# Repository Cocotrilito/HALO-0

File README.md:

# HALO-0
HALO-0 is a custom development board built around the RP2040 System-on-Chip (SoC).this features a quad memory flash a crystal oscillator, a voltage regulator and a USB C. adding to the repos thematic the HALO-0 has a quote of doubting the impossible and a masterpiece, NAPOLEON TO THE MUNA!

## The reason behind this project
This project started as a following up to the guide provided by *https://github.com/KaiPereira* the teacher or the one for making this project possible, basically my goal was to learn the fundamentals of schematic and routing, and learn everything about how an actual pcb works, cause I've already made two, but really basic ones.. so with this project I was able to open more my eyes, and learn a bit more about everything (USB, MEMORY FLASH, CRYSTAL OSCILATORS, VOLTAGE REGULATORS, CAPACITORS, RESISTANCES, ETC). BUT I did not ended there so I added my OWN style of art, based on my personal preferences (napoleon). and I also added a quote that helped me be disciplined with HackClub Stasis!. its an easter egg hahaha.

## Schematic Overview

this is the schematic 

-

## PCB - DIFERENT VERSIONS

## RENDER!!

## BOM

| Name | Purpose | Qty | Cost (USD) | Distributor
|-----:|----------|----------|-------|-------|
| RP2040 (U1) | Brain of the PCB | 1 | $4.89 | JLCPCB / LCSC |
| W25Q16JVUXIQ | Memory for the PCB | 1 | $5.07 | JLCPCB / LCSC |
| TYPE-C-31-M-12 | USB C Energy & Data | 1 | $0.91 | JLCPCB / LCSC |
| KT-0603R (D1) | LED RED (Cohete Art) | 1 | $0.03 | JLCPCB / LCSC |
|RC0603JR-071KL (R8) | 1k LED resistor | 1 | $0.03 | JLCPCB / LCSC |
| MCP1700T-3302E/TT | Voltage regulator | 1 | $2.43 | JLCPCB / LCSC |
| X322512MSB4SI | Crystal 12Mhz | 1| $0.36 | JLCPCB / LCSC |
| TS-1088-AR02016 | SMD BUTTON | 2 | $0.27 | JLCPCB / LCSC |
| C13-14 10uF | Regulator capacitor | 2 | $0.01 | JLCPCB / LCSC |
| "C1, C10 1uF" | Energy input +1v1 | 2 | $0.01 | JLCPCB / LCSC |
| C2-C9 100nF | Decoupling caps | 8 | $0.01 | JLCPCB / LCSC |

## Final notes!
Thanks for reading! made possible with http://stasis.hackclub.com/
-/
## me
*By cocotrilo*
**made with luv (THIS ONE WAS WITH HATE) jk <3**

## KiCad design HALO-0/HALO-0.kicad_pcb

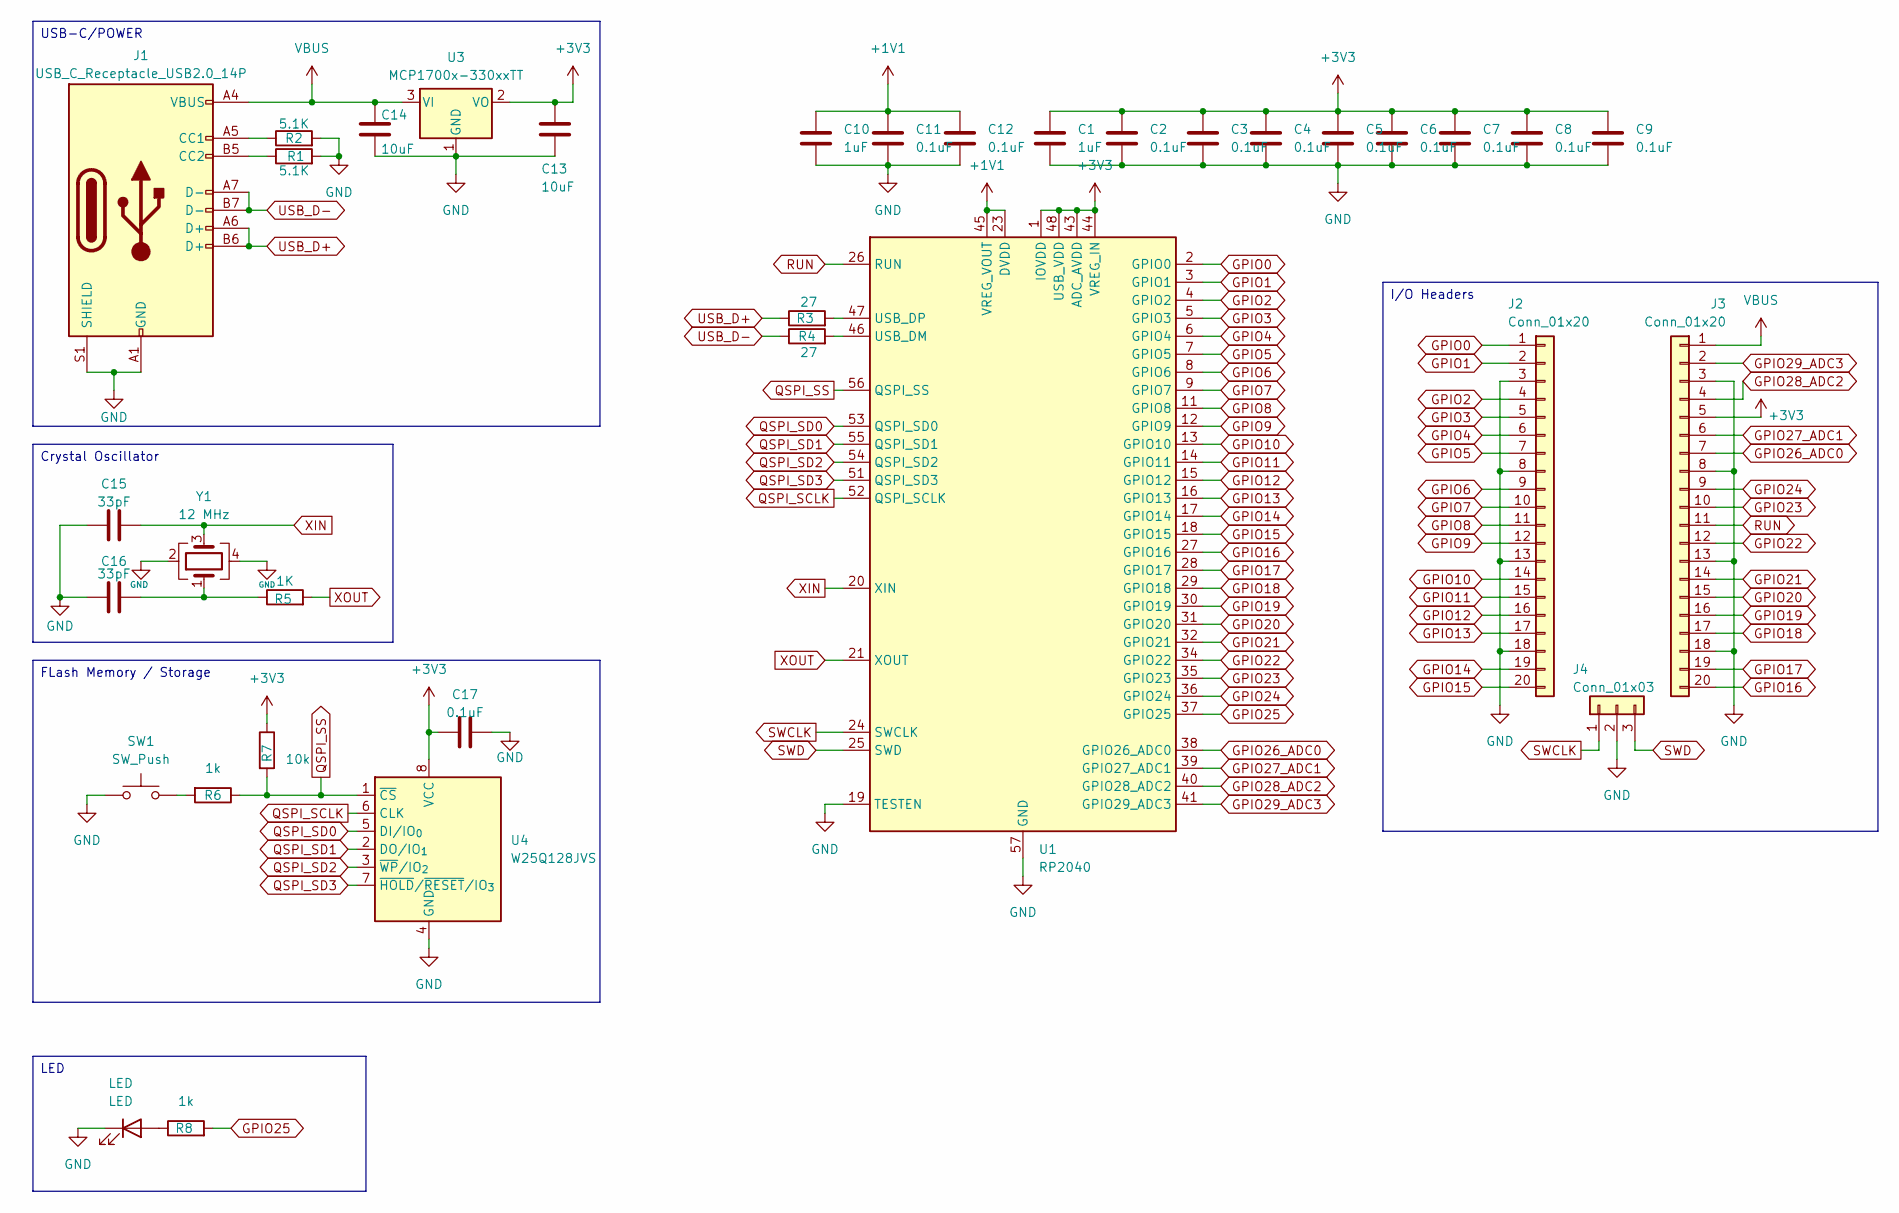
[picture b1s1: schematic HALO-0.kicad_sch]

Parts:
C1, C10: 1uF; C_0402_1005Metric
C2, C3, C4, C5, C6, C7, C8, C9, C11, C12, C17: 0.1uF; C_0402_1005Metric
C13, C14: 10uF; C_0603_1608Metric
C15, C16: 33pF; C_0402_1005Metric
J1: USB_C_Receptacle_USB2.0_14P; USB_C_Receptacle_HRO_TYPE-C-31-M-12
J2, J3: Conn_01x20; PinHeader_1x20_P2.54mm_Vertical
J4: Conn_01x03; PinHeader_1x03_P2.54mm_Vertical
LED: LED; LED_0603_1608Metric
R1, R2: 5.1K; R_0402_1005Metric
R3, R4: 27; R_0402_1005Metric
R5: 1K; R_0402_1005Metric
R6: 1k; R_0402_1005Metric
R7: 10k; R_0402_1005Metric
R8: 1k; R_0603_1608Metric
SW1: SW_Push; SW_Push_SPST_NO_Alps_SKRK
U1: RP2040; QFN-56-1EP_7x7mm_P0.4mm_EP3.2x3.2mm
U3: MCP1700x-330xxTT; SOT-23
U4: W25Q128JVS; Winbond_USON-8-1EP_3x2mm_P0.5mm_EP0.2x1.6mm
Y1: 12 MHz; Crystal_SMD_3225-4Pin_3.2x2.5mm

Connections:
+1V1: C10.1, C11.1, C12.1, U1.23 (DVDD), U1.45 (VREG_VOUT), U1.50 (DVDD)
+3V3: C1.1, C2.1, C3.1, C4.1, C5.1, C6.1, C7.1, C8.1, C9.1, C13.1, C17.1, J3.5, R7.1, U1.1 (IOVDD), U1.10 (IOVDD), U1.22 (IOVDD), U1.33 (IOVDD), U1.42 (IOVDD), U1.43 (ADC_AVDD), U1.44 (VREG_IN), U1.48 (USB_VDD), U1.49 (IOVDD), U3.2 (VO), U4.8 (VCC)
GND: C1.2, C2.2, C3.2, C4.2, C5.2, C6.2, C7.2, C8.2, C9.2, C10.2, C11.2, C12.2, C13.2, C14.2, C15.1, C16.1, C17.2, J1.A1 (GND), J1.A12 (GND), J1.B1 (GND), J1.B12 (GND), J1.S1 (SHIELD), J2.3, J2.8, J2.13, J2.18, J3.3, J3.8, J3.13, J3.18, J4.2, LED.1 (K), R1.2, R2.2, SW1.1, U1.19 (TESTEN), U1.57 (GND), U3.1 (GND), U4.4 (GND), Y1.2, Y1.4; also elsewhere on the board
GPIO0: J2.1, U1.2 (GPIO0)
GPIO1: J2.2, U1.3 (GPIO1)
GPIO2: J2.4, U1.4 (GPIO2)
GPIO3: J2.5, U1.5 (GPIO3)
GPIO4: J2.6, U1.6 (GPIO4)
GPIO5: J2.7, U1.7 (GPIO5)
GPIO6: J2.9, U1.8 (GPIO6)
GPIO7: J2.10, U1.9 (GPIO7)
GPIO8: J2.11, U1.11 (GPIO8)
GPIO9: J2.12, U1.12 (GPIO9)
GPIO10: J2.14, U1.13 (GPIO10)
GPIO11: J2.15, U1.14 (GPIO11)
GPIO12: J2.16, U1.15 (GPIO12)
GPIO13: J2.17, U1.16 (GPIO13)
GPIO14: J2.19, U1.17 (GPIO14)
GPIO15: J2.20, U1.18 (GPIO15)
GPIO16: J3.20, U1.27 (GPIO16)
GPIO17: J3.19, U1.28 (GPIO17)
GPIO18: J3.17, U1.29 (GPIO18)
GPIO19: J3.16, U1.30 (GPIO19)
GPIO20: J3.15, U1.31 (GPIO20)
GPIO21: J3.14, U1.32 (GPIO21)
GPIO22: J3.12, U1.34 (GPIO22)
GPIO23: J3.10, U1.35 (GPIO23)
GPIO24: J3.9, U1.36 (GPIO24)
GPIO25: R8.2, U1.37 (GPIO25)
GPIO26_ADC0: J3.7, U1.38 (GPIO26_ADC0)
GPIO27_ADC1: J3.6, U1.39 (GPIO27_ADC1)
GPIO28_ADC2: J3.4, U1.40 (GPIO28_ADC2)
GPIO29_ADC3: J3.2, U1.41 (GPIO29_ADC3)
unnamed: C16.2, R5.1, Y1.1
unnamed 34: LED.2 (A), R8.1; also elsewhere on the board
unnamed: J1.A5 (CC1), R2.1
unnamed: J1.B5 (CC2), R1.1
unnamed: R6.2, SW1.2
unnamed: R4.2, U1.46 (USB_DM)
unnamed: R3.2, U1.47 (USB_DP)
QSPI_SCLK: U1.52 (QSPI_SCLK), U4.6 (CLK)
QSPI_SD0: U1.53 (QSPI_SD0), U4.5 (DI/IO_{0})
QSPI_SD1: U1.55 (QSPI_SD1), U4.2 (DO/IO_{1})
QSPI_SD2: U1.54 (QSPI_SD2), U4.3 (~WP/IO_{2})
QSPI_SD3: U1.51 (QSPI_SD3), U4.7 (~HOLD/~RESET/IO_{3})
QSPI_SS: R6.1, R7.2, U1.56 (QSPI_SS), U4.1 (~CS)
RUN: J3.11, U1.26 (RUN)
SWCLK: J4.1, U1.24 (SWCLK)
SWD: J4.3, U1.25 (SWD)
USB_D+: J1.A6 (D+), J1.B6 (D+), R3.1
USB_D-: J1.A7 (D-), J1.B7 (D-), R4.1
VBUS: C14.1, J1.A4 (VBUS), J1.A9 (VBUS), J1.B4 (VBUS), J1.B9 (VBUS), J3.1, U3.3 (VI)
XIN: C15.2, U1.20 (XIN), Y1.3
XOUT: R5.2, U1.21 (XOUT)

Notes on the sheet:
I/O Headers
USB-C/POWER
Crystal Oscillator
LED
FLash Memory / Storage

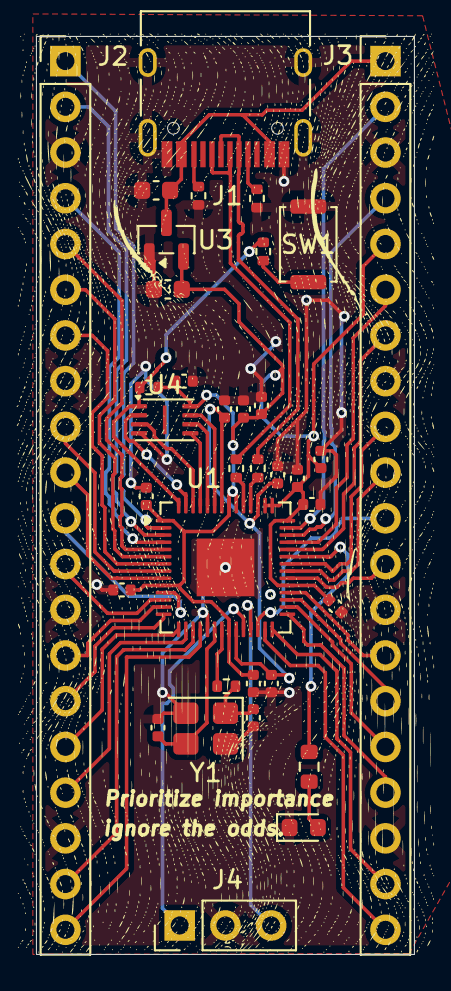
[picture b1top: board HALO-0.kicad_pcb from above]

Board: 2 copper layers, 21.0 x 51.0 mm, 35 parts (0 on the bottom side), 54 nets.

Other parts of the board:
D1: LED; LED_0603_1608Metric

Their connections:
GND: D1.1 (K); also elsewhere on the board
unnamed 34: D1.2 (A); also elsewhere on the board

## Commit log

2026-04-18 HALO-O FINISHED, adding images and the project foles for shipment
2026-04-18 Update README with project details and BOM
    Expanded project description, added schematic overview, PCB versions, BOM, and final notes.
2026-04-18 Revise README for clarity and grammatical accuracy
    Corrected grammar and clarified project goals in the README.
